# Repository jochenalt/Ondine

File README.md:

# Ondine
Ondine is a lovely ballet of robots. Right in the middle of development. Check the [Documentation](http://ondine.readthedocs.io). Contact me via the [hackaday page](https://hackaday.io/post/53678).

### Contents
    /cad 	    CAD designs in Inventor 2018
    /theory     mainly on kinematics
    /code       source code (mainly C++)
    /schematics schematics in EAGLE 
    /docs		source of Ondine's [Documentation](https://http://ondine.readthedocs.io)
    /datasheets datasheets of components Ondine is made of

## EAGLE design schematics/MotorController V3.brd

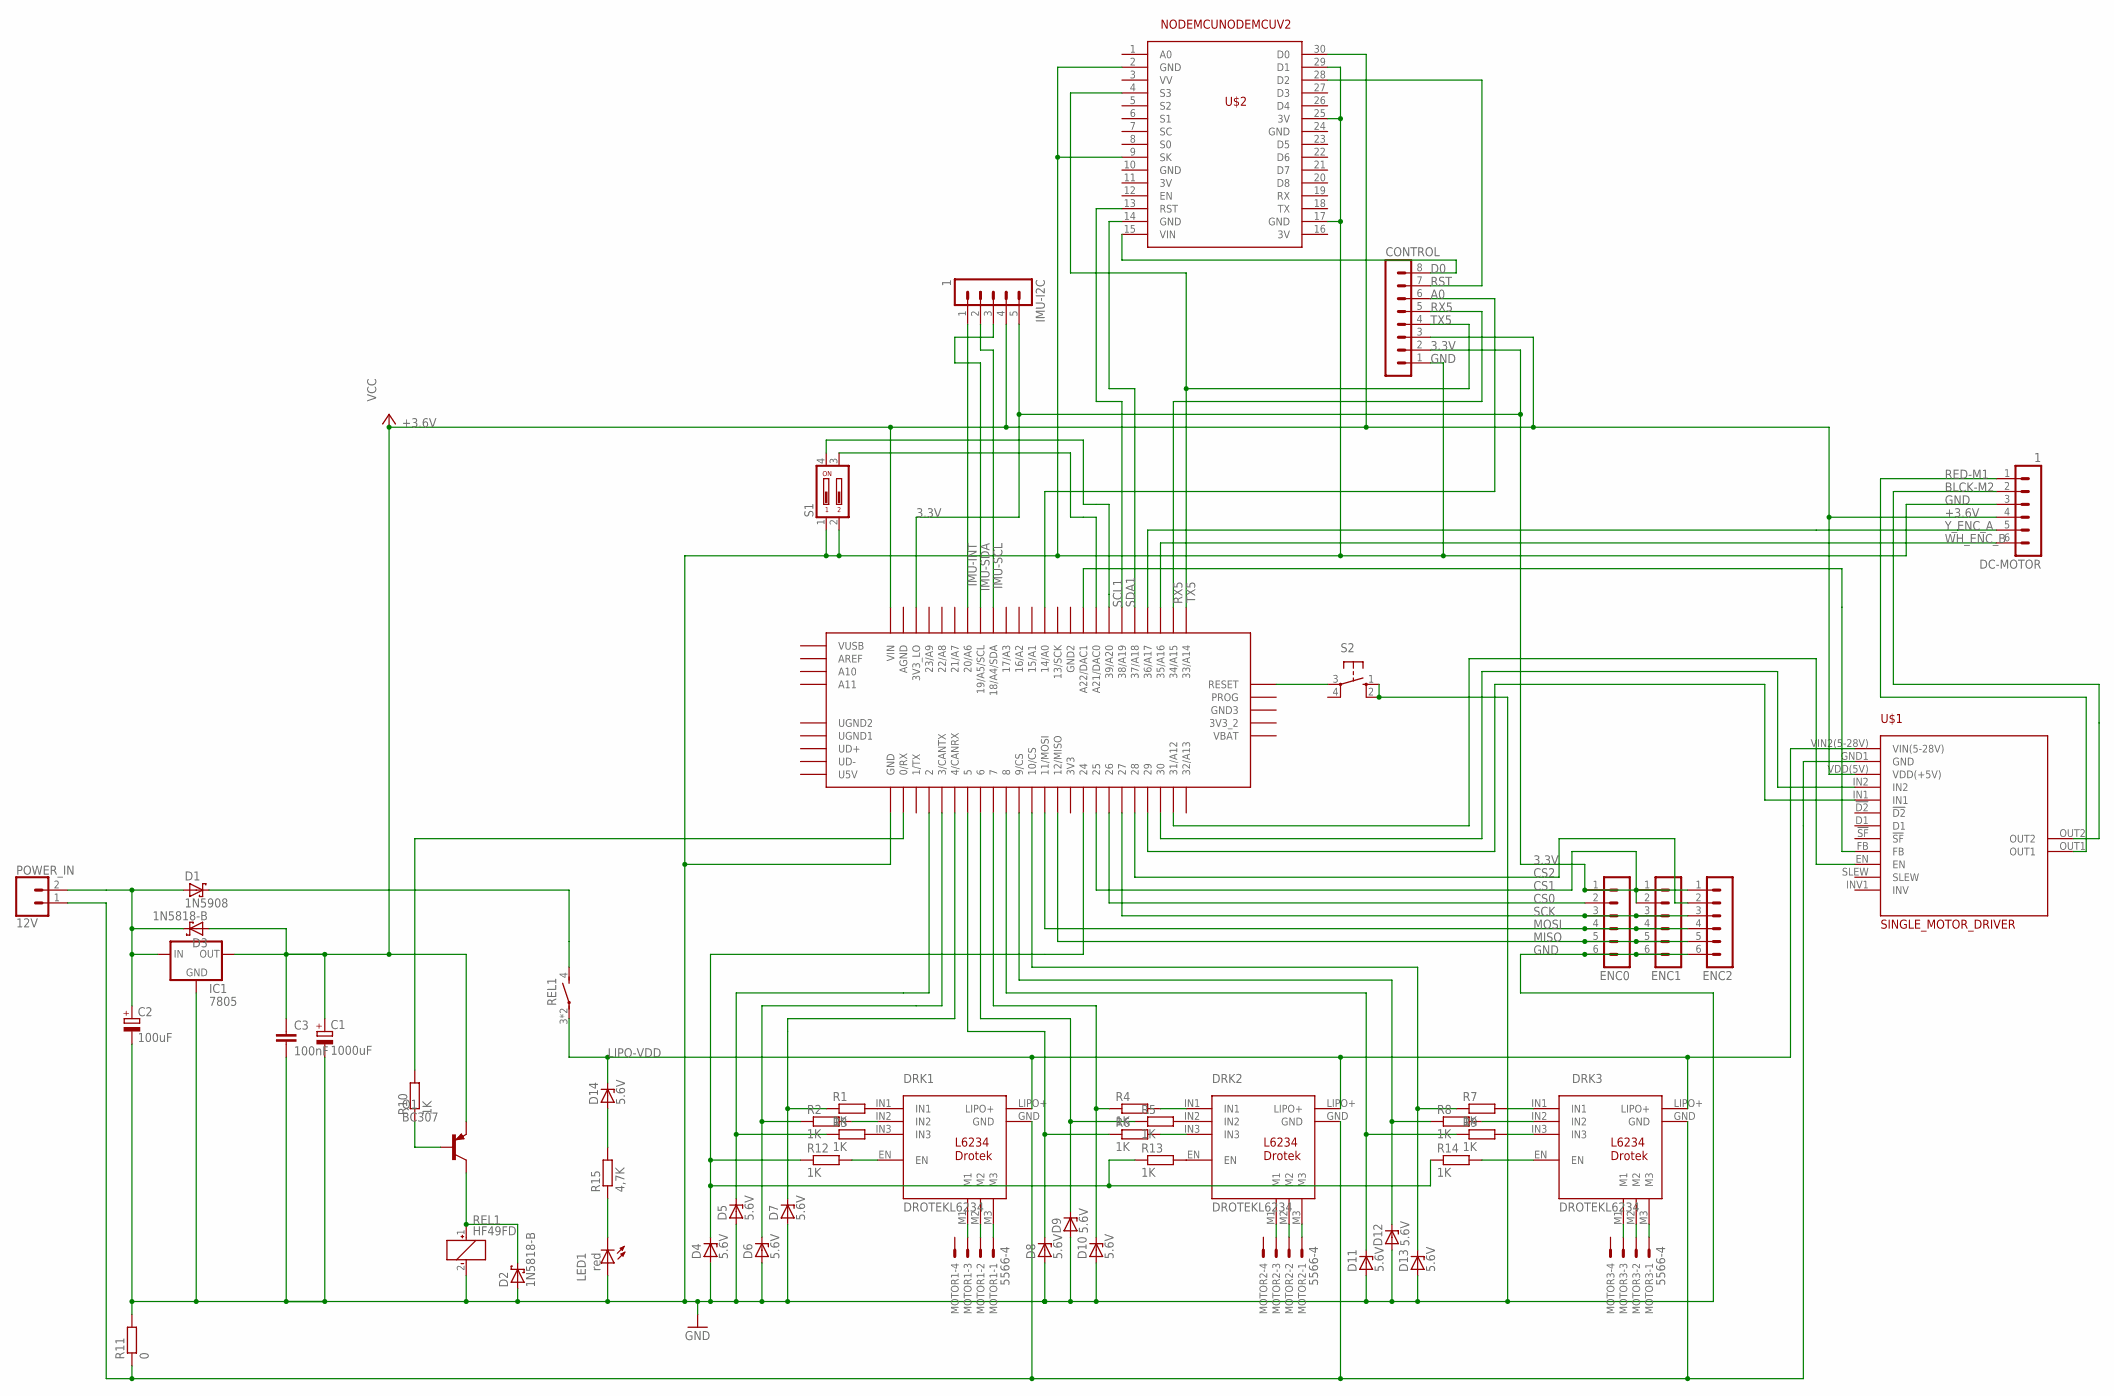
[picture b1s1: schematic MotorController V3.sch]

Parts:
C1: 1000uF; E2,5-6
C2: 100uF; E5-5
C3: 100nF; C2.5-2
CONTROL: MA08-1
D1: 1N5908; C4111-15
D2, D3: 1N5818-B; DO41-7.6
D4, D5, D6, D7, D8, D9, D10, D11, D12, D13, D14: 5.6V; DO41Z10
DC-MOTOR: 1; MA06-1
DRK1, DRK2, DRK3: DROTEKL6234
ENC0, ENC1, ENC2: MA06-1
IC1: 7805; 78XXS
IMU-I2C: 1; MA05-1
LED1: red; LED3MM
MOTOR1, MOTOR2, MOTOR3: 5566-4
POWER_IN: 12V; SCREWTERMINAL-3.5MM-2
PRJ1: TEENSY_3.5/3.6
Q1: BC307; TO92
R1, R2, R3, R4, R5, R6, R7, R8, R9, R10, R12, R13, R14: 1K; 0207/10
R11: 0; 0204V
R15: 4,7K; 0207/10
REL1: HF49FD
S1: DIP02YL
S2: B3F-10XX
U$1: SINGLE_MOTOR_DRIVER; MOTOR_DRIVER_MC33926_FOOTPRINT_
U$2: NODEMCUNODEMCUV2; NODEMCUV2

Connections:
3.3V: CONTROL.2, ENC0.1, ENC1.1, ENC2.1, IMU-I2C.5, PRJ1.3V3_LO
3V: U$2.11 (3V), U$2.16 (3V)
+3.6V: C1.+, C3.1, CONTROL.3, D3.A, DC-MOTOR.4, IC1.OUT, IMU-I2C.4, PRJ1.VIN, Q1.1 (E), U$1.VDD(5V) (VDD(+5V)), U$2.30 (D0)
A0: CONTROL.6, PRJ1.14/A0
BLCK-M2: DC-MOTOR.2, U$1.OUT2
CS0: ENC0.2, PRJ1.26
CS1: ENC1.2, PRJ1.25
CS2: ENC2.2, PRJ1.28
D0: CONTROL.8, U$2.15 (VIN)
GND: C1.-, C2.-, C3.2, CONTROL.1, D2.A, D4.A, D5.A, D6.A, D7.A, D8.A, D9.A, D10.A, D11.A, D12.A, D13.A, DC-MOTOR.3, ENC0.6, ENC1.6, ENC2.6, IC1.GND, LED1.A, PRJ1.GND, R11.2, REL1.2 (-), S1.1, S1.2, S2.1 (S), S2.2 (S1), U$2.2 (GND), U$2.9 (SK), U$2.10 (GND), U$2.17 (GND), U$2.24 (GND), U$2.25 (3V), U$2.29 (D1)
IMU-INT: IMU-I2C.1, PRJ1.20/A6
IMU-SCL: IMU-I2C.2, PRJ1.18/A4/SDA
IMU-SDA: IMU-I2C.3, PRJ1.19/A5/SCL
LIPO-GND: DRK1.GND, DRK2.GND, DRK3.GND, POWER_IN.1, R11.1, U$1.GND1 (GND)
LIPO-VDD: D14.C, DRK1.LIPO+, DRK2.LIPO+, DRK3.LIPO+, REL1.3, REL1.5, U$1.VIN2(5-28V) (VIN(5-28V))
MISO: ENC0.5, ENC1.5, ENC2.5, PRJ1.12/MISO
MOSI: ENC0.4, ENC1.4, ENC2.4, PRJ1.11/MOSI
unnamed: DRK1.M1, MOTOR1.3
unnamed: DRK1.M2, MOTOR1.2
unnamed: DRK1.M3, MOTOR1.1
unnamed: DRK1.IN1, R1.2
unnamed: DRK1.IN2, R2.2
unnamed: DRK1.IN3, R3.2
unnamed: D7.C, PRJ1.4/CANRX, R1.1
unnamed: D6.C, PRJ1.3/CANTX, R2.1
unnamed: D5.C, PRJ1.2, R3.1
unnamed: DRK3.EN, R14.2
unnamed: DRK2.IN1, R4.2
unnamed: PRJ1.21/DAC0 (A21/DAC0), S1.3
unnamed: DRK2.M1, MOTOR2.3
unnamed: DRK2.M2, MOTOR2.2
unnamed: DRK2.M3, MOTOR2.1
unnamed: DRK3.M1, MOTOR3.3
unnamed: DRK3.M2, MOTOR3.2
unnamed: DRK3.M3, MOTOR3.1
unnamed: DRK2.IN2, R5.2
unnamed: DRK2.IN3, R6.2
unnamed: D8.C, PRJ1.5, R6.1
unnamed: D9.C, PRJ1.6, R5.1
unnamed: D10.C, PRJ1.7, R4.1
unnamed: DRK3.IN2, R8.2
unnamed: DRK3.IN1, R7.2
unnamed: DRK3.IN3, R9.2
unnamed: D11.C, PRJ1.8, R9.1
unnamed: D12.C, PRJ1.9/CS, R8.1
unnamed: D13.C, PRJ1.10/CS, R7.1
unnamed: Q1.2 (B), R10.1
unnamed: D2.C, Q1.3 (C), REL1.1 (+)
unnamed: C2.+, D1.A, D3.C, IC1.IN, POWER_IN.2
unnamed: D14.A, R15.2
unnamed: LED1.K (C), R15.1
unnamed: D1.C, REL1.4 (S)
unnamed: PRJ1.39/A20, S1.4
unnamed: PRJ1.0/RX, R10.2
unnamed: DRK1.EN, R12.2
unnamed: PRJ1.29, U$1.IN1
unnamed: PRJ1.31/A12, U$1.EN
unnamed: D4.C, PRJ1.24, R12.1, R13.1, R14.1
unnamed: PRJ1.30, U$1.IN2
unnamed: DRK2.EN, R13.2
unnamed: PRJ1.RESET, S2.3
unnamed: PRJ1.A22/DAC1, U$1.FB
RED-M1: DC-MOTOR.1, U$1.OUT1
RST: CONTROL.7, U$2.28 (D2)
RX5: CONTROL.5, PRJ1.34/A15
SCK: ENC0.3, ENC1.3, ENC2.3, PRJ1.27
SCL1: PRJ1.38/A19, U$2.13 (RST)
SDA1: PRJ1.37/A18, U$2.14 (GND)
TX5: CONTROL.4, PRJ1.33/A14, U$2.4 (S3)
WH_ENC_B: DC-MOTOR.6, PRJ1.35/A16
Y_ENC_A: DC-MOTOR.5, PRJ1.36/A17

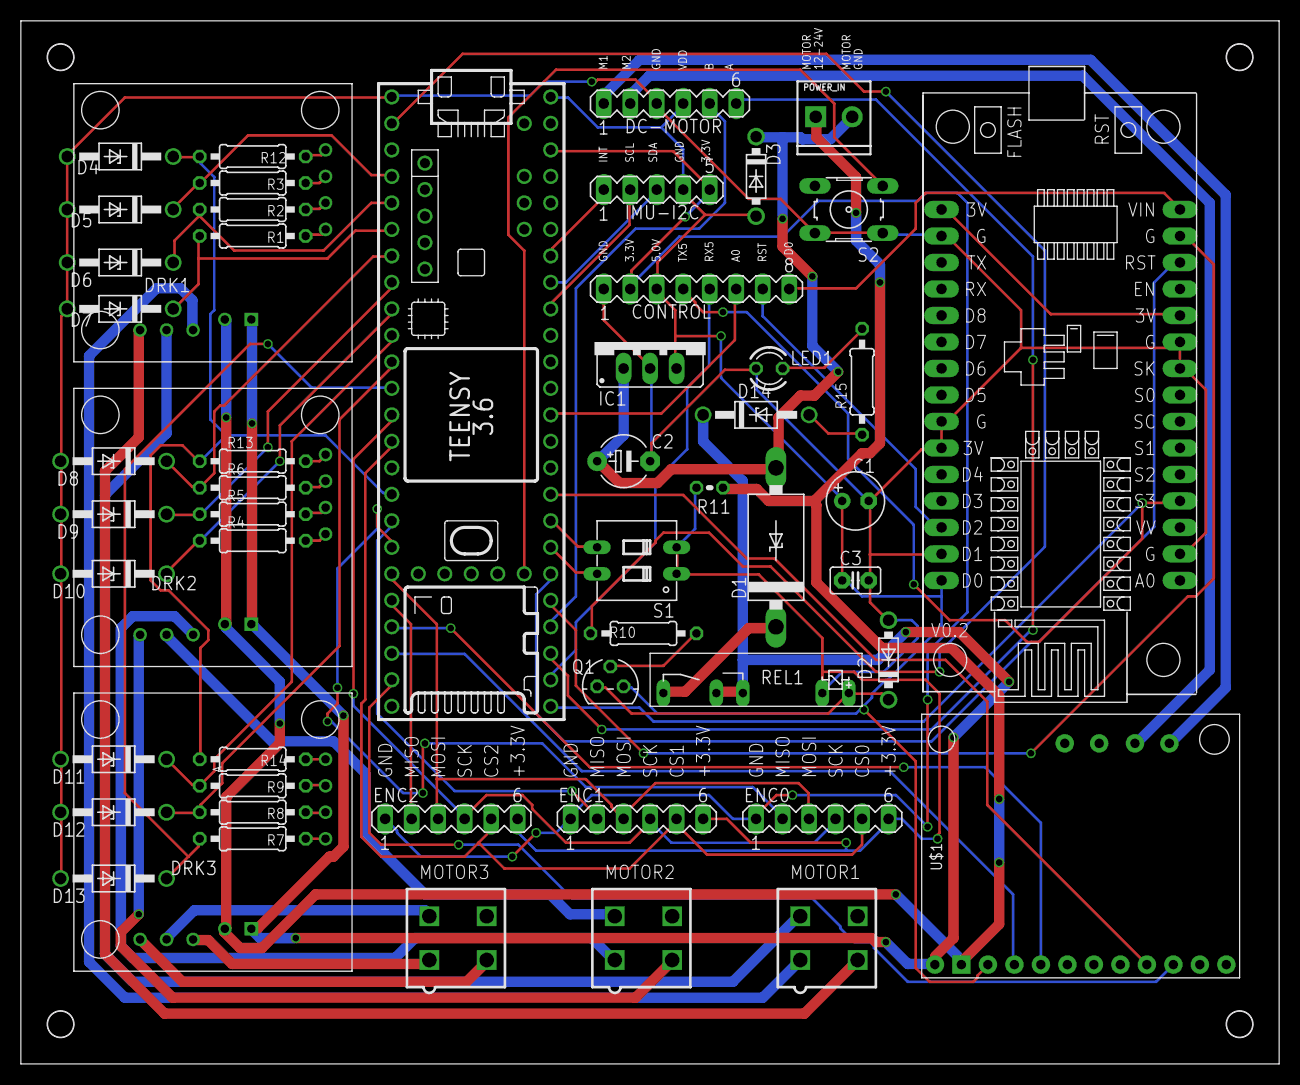
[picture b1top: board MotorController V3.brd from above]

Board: 2 copper layers, 120.5 x 99.8 mm, 54 parts (0 on the bottom side), 71 nets.

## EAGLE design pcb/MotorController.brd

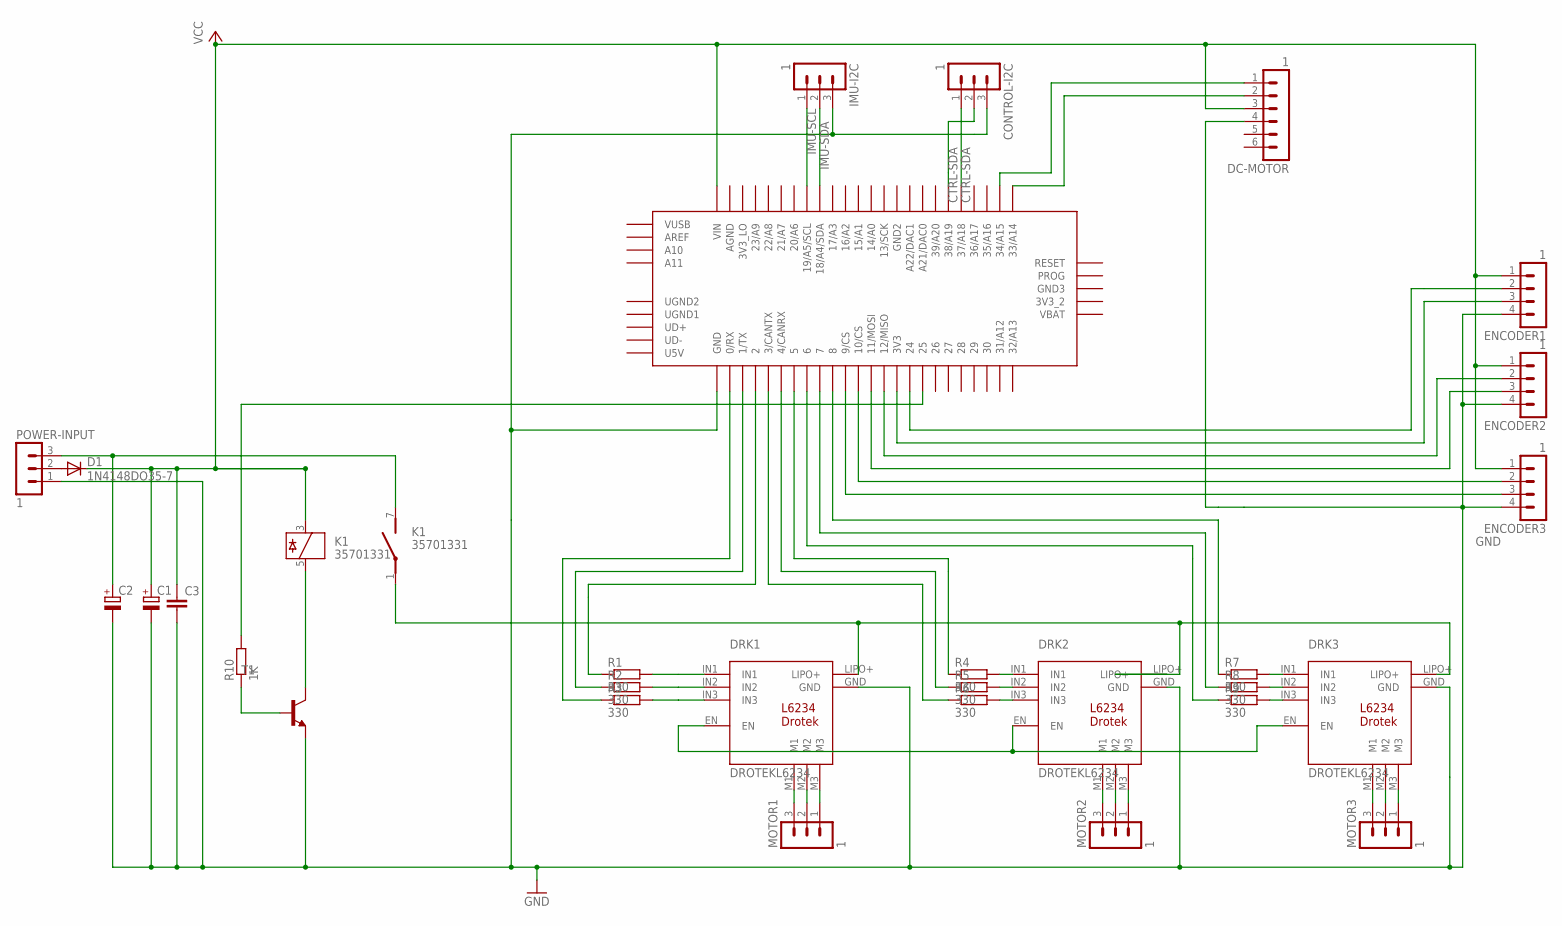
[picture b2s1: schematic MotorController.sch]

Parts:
C1, C2: CPOL-EUE7.5-16; E7,5-16
C3: C2.5/2; C2.5-2
CONTROL-I2C: 1; MA03-1
D1: 1N4148DO35-7; DO35-7
DC-MOTOR: 1; MA06-1
DRK1, DRK2, DRK3: DROTEKL6234
ENCODER1, ENCODER2, ENCODER3: 1; MA04-1
IMU-I2C: 1; MA03-1
K1: 35701331; REED
MOTOR1, MOTOR2, MOTOR3: 1; MA03-1
POWER-INPUT: 1; MA03-1
PRJ1: TEENSY_3.5/3.6
R1, R2, R3, R4, R5, R6, R7, R8, R9: 330; 0204/7
R10: 1K; 0204/7
T1: -NPN-TO92; TO92

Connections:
CTRL-SDA: CONTROL-I2C.1, PRJ1.37/A18
GND: C1.-, C2.-, C3.2, CONTROL-I2C.3, DC-MOTOR.4, DRK1.GND, DRK2.GND, DRK3.GND, ENCODER1.4, ENCODER2.4, ENCODER3.4, IMU-I2C.3, POWER-INPUT.1, PRJ1.GND, T1.1 (E)
IMU-SCL: IMU-I2C.1, PRJ1.19/A5/SCL
IMU-SDA: IMU-I2C.2, PRJ1.18/A4/SDA
unnamed: DRK1.M1, MOTOR1.3
unnamed: DRK1.M2, MOTOR1.2
unnamed: DRK1.M3, MOTOR1.1
unnamed: DRK1.IN1, R1.2
unnamed: DRK1.IN2, R2.2
unnamed: DRK1.IN3, R3.2
unnamed: PRJ1.2, R1.1
unnamed: PRJ1.1/TX, R2.1
unnamed: PRJ1.0/RX, R3.1
unnamed: DRK1.EN, DRK2.EN, DRK3.EN
unnamed: DRK2.IN1, R4.2
unnamed: DRK1.LIPO+, DRK2.LIPO+, DRK3.LIPO+, K1.1
unnamed: DRK2.M1, MOTOR2.3
unnamed: DRK2.M2, MOTOR2.2
unnamed: DRK2.M3, MOTOR2.1
unnamed: DRK3.M1, MOTOR3.3
unnamed: DRK3.M2, MOTOR3.2
unnamed: DRK3.M3, MOTOR3.1
unnamed: DRK2.IN2, R5.2
unnamed: DRK2.IN3, R6.2
unnamed: PRJ1.3/CANTX, R6.1
unnamed: PRJ1.4/CANRX, R5.1
unnamed: PRJ1.5, R4.1
unnamed: DRK3.IN2, R8.2
unnamed: DRK3.IN1, R7.2
unnamed: DRK3.IN3, R9.2
unnamed: PRJ1.6, R9.1
unnamed: PRJ1.7, R8.1
unnamed: PRJ1.8, R7.1
unnamed: R10.1, T1.2 (B)
unnamed: K1.5, T1.3 (C)
unnamed: C2.+, K1.7 (S), POWER-INPUT.3
unnamed: ENCODER3.3, PRJ1.9/CS
unnamed: ENCODER3.2, PRJ1.10/CS
unnamed: ENCODER2.3, PRJ1.11/MOSI
unnamed: ENCODER2.2, PRJ1.12/MISO
unnamed: ENCODER1.3, PRJ1.3V3
unnamed: ENCODER1.2, PRJ1.24
unnamed: D1.A, POWER-INPUT.2
unnamed: DC-MOTOR.2, PRJ1.33/A14
unnamed: DC-MOTOR.1, PRJ1.34/A15
unnamed: PRJ1.25, R10.2
unnamed: CONTROL-I2C.2, PRJ1.38/A19
VCC: C1.+, C3.1, D1.C, DC-MOTOR.3, ENCODER1.1, ENCODER2.1, ENCODER3.1, K1.3, PRJ1.VIN

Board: 2 copper layers, 30 parts (0 on the bottom side), 48 nets, no tracks yet.

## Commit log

2018-06-24 no message
2018-06-25 omniwheel with mounting hub
2018-06-25 forgotten files
2018-06-26 new Omniwheel 70mm
2018-06-27 0.25 more space between rolls and spoke
2018-06-30 Friction surface of omniwheel rols adapted
2018-07-01 Added Maxxon Motor
2018-07-01 print of omniwheel with space for corund
2018-07-02 added prototypes
2018-07-06 round enclosure
2018-07-07 built and corrected omniwheel
2018-07-07 Zahnriemenscheiben
2018-07-11 London-remote Druckauftrag
2018-07-12 london
2018-07-13 Druck nach London
2018-07-13 enlarged bearings in planetary gear
2018-07-14 corrected big rolls in Omni wheels (tighter bearing space)
2018-07-14 fixed and centered encoder within enclosure
2018-07-15 planetary Gear bearing correction
2018-07-16 back to helical gearing
2018-07-16 replace old enclosure by leaner shape
2018-07-17 adapted teeth shape
2018-07-18 Revert "adapted teeth shape"
    This reverts commit 82a1961c36844213699828fc2cebeaf81ce44edd.
2018-07-18 Revert "Revert "adapted teeth shape""
    This reverts commit 169dd93047d1f5d752c282b07249b5d372d47a6e.
2018-07-18 made planetary gear wider
2018-07-21 Cycloidal Gear
2018-07-21 increased modul to 1.0 of planetary gear
2018-07-22 remote print
2018-07-22 made omniwheel small started with form
2018-07-22 Have a choice of omniwheels
2018-07-23 changed cycloid gear equations
2018-07-24 Form got a threaded rod to move
2018-07-26 Cycloidal Gear print
2018-07-26 Planetary Gear tolerance adaptions
2018-07-29 Beltdrive
2018-07-29 reorganized
2018-07-29 removed unnecessary stuff
2018-07-29 fixed Beltdrive files
2018-07-29 status
2018-07-29 Sunday-Print
2018-07-30 omniwheel looks good
2018-07-31 2.nd try cycloid gear
2018-07-31 drive
2018-07-31 OmniWheel with 6mm bearings
2018-07-31 Print after Cocktails
2018-08-02 small amendments
2018-08-02 Start of BLDC code
2018-08-02 weekenedprint
2018-08-04 Motor is turning
2018-08-05 weekend
2018-08-05 blindly coded new controller with encoder
2018-08-07 London calling
2018-08-10 new BLDC driver implementation turns
2018-08-11 startup procedure
2018-08-11 cleanup
2018-08-11 tuned overheating
2018-08-13 beltdrive tuned
2018-08-14 Worked on Form
2018-08-14 Made Beltdriver tighter and adapted omniwheel to 2x5x2 bearings
2018-08-16 Revert "no message"
    This reverts commit d3c9e16ff2c76921861703b5b18a575ad4147334.
2018-08-18 beltdrive wheels got a flange
2018-08-18 completed omniwheel
2018-08-19 updated drotek and pololu library
2018-08-19 removed flanges of wheels again
2018-08-20 constant distance from belt to enclosure
2018-08-20 created engine and generic menu management
2018-08-26 Motor too weak and gets too hot. Mist.
2018-08-28 Badminton Print
2018-08-29 read a lot of stuff about brushless motors
2018-08-29 read even more on brushless motors
2018-08-30 implemented self-tuning fuzzy PID controller
2018-09-01 made pulleys a tommy to let them centre theirselves
2018-09-01 made startup of brushless motor more stable
2018-09-02 gave belt bearing bigger bearings
2018-09-02 mondayprint
2018-09-05 First print of bottom sphere
2018-09-09 ordered PCB
2018-09-14 Smaller Omniwheel holder
2018-09-16 Weekend before Monday print
2018-09-19 up to body print
2018-09-22 assembled engine and trying out new pcb
2018-09-24 AfterWeekend
2018-09-30 accelerated bldc setup
2018-10-03 first draft of Webserver
2018-10-04 i2c between webserver and bot controller
2018-10-04 board now with ESP8266
2018-10-05 new class I2CMaster
2018-10-05 introduced I2CSlave
2018-10-05 ordered PCB !
2018-10-05 introduced BallDrive
2018-10-05 made motor more stiff in position control
2018-10-07 made balldrive run
2018-10-08 comments
2018-10-10 added null value in IMU
2018-10-10 re-arranged groups
2018-10-12 added new project code/common
2018-10-13 tried out kinematic
2018-10-13 Pictures
2018-10-14 reorganized EEPROM memory
2018-10-20 ESP8266 NodeMCU V2 foot print corrected
2018-10-20 calibrated PID of lifter motor
2018-10-20 PCB Holder correction(Teensy USB blocked was blocked by holder)
2018-10-22 adapted PCB Holder to not have legs right at the USB port
2018-10-22 conflu
2018-10-26 startup phase
2018-10-27 more aggressive Motor PID
2018-10-27 bugfix: torque reduction after friction has been overcome should happens once only
2018-10-27 aligned coord systems of IMU and kinematics
2018-10-27 documentation
2018-10-27 bugfix in log output
2018-10-27 new layout such that sockets can be reached
2018-11-03 preparation for saturday
2018-11-03 state tuning menu
2018-11-03 tons of adaptions as preparation to state control
2018-11-03 added comments
2018-11-03 made logger optional
2018-11-03 log msg
2018-11-03 added time measurement
2018-11-03 added logging
2018-11-03 added time measurements
2018-11-03 prologed delay after turning power on
2018-11-03 cleaned up code
2018-11-04 first state tuning
2018-11-04 logged position
2018-11-04 weekend's done
2018-11-07 heavy rewriting after first balancing trials
2018-11-10 does not yet balance
2018-11-12 moved away from mm and mm/s towards m and m/s
2018-11-14 Started V3 of Enclosure
2018-11-16 V3 Enclosure
2018-11-18 Replaced optical encoder by magnetic absolute encoders
2018-11-19 LegNotch
2018-11-21 Worm gear for leg
2018-11-24 almost ready to print
2018-11-24 print of V3
2018-11-26 printing Torus
2018-11-28 Made PCB scaffold fit into barrel
2018-11-28 added switch in body's hat
2018-11-29 reorganized code
2018-12-01 Bugfix: magnetic field fixed for negative angles
2018-12-02 introduced two-folded legs
2018-12-02 barrel/torus connector
2018-12-02 new assembly
2018-12-03 Ordered PCB by Aisler!
2018-12-08 Bugfix in angle computation of IMU
2018-12-09 balancing at 0 set point works, but disturbances are not yet compensated
2018-12-09 playing with state control
2018-12-09 cleaned up timing
2018-12-12 introduced FIFO to access IMU
2018-12-15 tmp2
2018-12-22 added MPU9150
2018-12-22 IMU failure
2018-12-23 regler is noch nicht toll
2019-01-05 Body has a planetary gear now
2019-01-05 improved body screws
2019-01-08 made sun hole in planetary gear bigger and space between motorholder and planets
2019-01-09 Model Simplification on planetary gear layer
2019-01-11 Motorholder got tighter, Planetary Sun got 0.2 more play
2019-01-13 Planetary Print
2019-01-20 First assembly of planetary gears

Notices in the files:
parts and their libraries:
SparkFun-Connectors: Licensing: Creative Commons ShareAlike 4.0 International - https://creativecommons.org/licenses/by-sa/4.0
diy-modules: Released under the Creative Commons Attribution 4.0 International License: http://creativecommons.org/licenses/by/4.0
